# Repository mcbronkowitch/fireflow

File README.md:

# FireFlow — a modulation-first ambient groovebox

A digital instrument built around a single idea: **modulation is the
instrument**. Two symmetric parts, each driven by a performable modulation
engine, feeding a selectable sound source.

It runs today on the desktop and inside VCV Rack. The hardware target is a
**standalone Daisy Patch Submodule prototype**, brought up in milestone M6.

**Build log, audio demos and photos:** [fireflow.ton-k.de](https://fireflow.ton-k.de/)

> **⚠️ Not yet running on hardware.** The modulation engine currently exists
> only as a portable C++ core, verified with the desktop **offline renderer**
> (unit tests + audio/CV render) and playable through the VCV Rack host.
> Selected CPU workloads have been measured on a real Daisy Seed, and the control
> hardware is being measured on a test coupon; the firmware that turns the engine
> into a playable device is milestone M6, and it has not been built.

## What makes it different

The **modulation system is the primary interface**, and the sound engine is
whatever you point it at — not a sound engine you happen to be able to
modulate.

Each part currently points at one of five: a **polyphonic synth voice**, a
**granular texture deck** that granulates live input or a loaded sample,
**WAVE**, a digital-glassy PPG-style wavetable voice, **BODY**, a resonator
that morphs along a physical axis from plucked string through prepared piano to
struck bell, or **BBD**, a voiceless bucket-brigade delay that processes
whatever reaches it — audio input or the other deck — instead of playing
notes. The deck is deliberately not a second melodic instrument — it
is the room the synth part plays in; WAVE covers the bell, vocal-formant,
hollow-resonant, and bright-digital corner; BODY is the struck and bowed one,
and it can be excited by its own echo, by the other deck, or by the audio
input; BBD is the one deck with nothing to trigger — it has no notes, so its
five modulation lanes drive the delay's clock, feedback and mix instead of
pitch and timbre, and its own voice row retunes ATTACK/DECAY/RESONANCE/SUB/
FILT into the delay's freeze, tail, feedback tilt, input level and loss-pole
brightness. All five sit behind the same five modulation lanes and the same
voice row, so no knob goes dead when you flip the engine.

That voice-row **SOURCE** control is contextual — **TIMB** on Synth, **FRAME**
on WAVE, **MATL** on BODY, **ORG** on Sampler, and **DRIVE** on BBD — while
**Detune A/B** remains an independent per-part setting.

On the texture deck, **STEP** walks a `SliceMap` of transients marked while the
buffer is recorded or loaded: each phrase fire spawns one grain on a real
attack in the material. MOTION moves that walk from ordered playback at zero
toward free traversal. **DENS** controls runtime grain overlap; **COLOR**
becomes **FEEL** in STEP, deriving accents from the material, and spreads the
cloud's pitch in FLOW. Material without enough transients falls back to the
even tempo grid automatically, so drones and pads stay playable. FLOW still
moves continuously across the same lanes regardless of engine.

Melodic **STEP** lanes keep two persistent full-pattern snapshots, A and B.
**FORM** chooses how those phrases are composed — TWO MOTIFS, ONE + VAR,
HIERARCHICAL, CALL / RESPONSE, or OSTINATO — while **SONG** independently
arranges them as AAAB, ABAB, ABBB, BUILD, ROTATE, MIRROR, or OFF. Structural
changes land on phrase boundaries; OFF keeps A evolving while B remains stored.
On the Rack panel the PLAY row is **STEP · FORM · SONG · NEW**. NEW rebuilds
the A/B pair and, on a Sampler, also spawns a grain immediately.

Those STEP notes are not all the same note. Each deck already ranks the slots
of its groove, and **DENSE** decides how far down that ranking it fires — so
the first slot to sound is the anchor and the ones DENSE reveals sit under it.
That ranking *is* the accent: it scales how hard a note is struck and how long
it rings (the ring-time half only once **DEC** is up), which gives a dense
pattern a contour instead of a machine pulse. No knob was added for it.

Each of the two **parts** is a **SuperModulator** — one performable macro
surface (RATE, SHAPE, DENSITY, SMOOTH, RANGE, MOD) sitting on top of
**five independent modulation lanes**, one per target. Every lane has its own
phase, its own random stream and its own probability dice, running at a fixed
musical ratio of the master rate. Shared character, independent motion: the
melody can rise while the filter falls. (A single output driving all targets
would just move everything in unison — a tremolo, not an instrument.)

Each lane can run as a smooth LFO (**FLOW**), a stepped sequence (**STEP**), or
grow, loop, or erode over time (**ENTROPY**). A center section -- **MORPH / COUPLE / DRIFT / SPOT / SETTLE** -- makes the
interaction between the two parts playable. One shared **Oliverb**-based
ambient reverb turns the room into an instrument (Doppler SIZE and a DECAY that
blooms past 100 %), while each deck has its own **SEND** dry/send mix into that
shared room (the centre **ROOM** group holds the reverb itself). CV + gate
outputs extend the modulation to the rest of the rack.

The full design intent lives in
[`docs/superpowers/specs/`](docs/superpowers/specs/); this README is a
self-contained summary of it.

## Architecture at a glance

One portable engine core, three hosts. No hardware type ever crosses into
`engine/`, so the exact same code runs in the desktop renderer, the VCV Rack
module, and (later) on the hardware prototype.

`Instrument` (`engine/instrument.h`) is the complete public API: `init(sample_rate)`,
normalized `0..1` parameter setters, and `process(in, out, size)`.

## Try it on the desktop (no hardware)

The engine is fully testable offline. You need a host C++ toolchain
(**clang** or gcc), **CMake**, and **Ninja**. doctest and nlohmann/json are
vendored under `third_party/`, so no test dependencies are fetched.

```bash
# optional: source a local env.sh to put your toolchain on PATH and set CC/CXX
source env.sh

cmake -S . -B build -DCMAKE_BUILD_TYPE=Release
cmake --build build
```

Run the unit tests:

```bash
ctest --test-dir build --output-on-failure
```

Configure with `-DCMAKE_BUILD_TYPE=Release`. Two of the six tests (`spky_tests`
and `ctrl_identity`) compare rendered audio against stored SHA-256 references,
and those were generated from an optimised build — a Debug configuration renders
slightly different floats and fails them with `SYNTH reference moved`.

Render a scenario to audio + a modulation trace. A scenario is a JSON timeline
of parameter changes (see `host/render/scenarios/`):

```bash
./build/render.exe host/render/scenarios/demo_step_melody.json out.wav mods.csv
```

This writes:

- **`out.wav`** — the rendered audio.
- **`mods.csv`** — every lane's output plus pitch CV / gate per part, decimated
  for plotting. Ideal for *seeing* what FLOW / STEP / MELODY actually do.

`demo_step_melody` is a good starting point: a fixed 16-step melody that loops
identically, then varies (GROW) or regenerates into new motivic phrases (RENEW)
as MELODY is dialled off center — and cycles the phrase principle.

## Play it now — VCV Rack (beta)

For a hands-on feel of the concept there's a **VCV Rack plugin** (`host/vcv/`)
that runs the same engine live — turn the knobs and hear the modulation engine
long before the M6 firmware. It's now a **beta**: real, playable Rack modules and
a permanent part of the workflow, not yet a finished instrument.

The plugin ships **two modules over the one engine core**. **FireFlow** is the
full surface: every engine setter on its own knob. **FireFlow HW Draft** is a
design study of the 60 HP hardware panel M6 is heading for, on the same engine.
Details in [`host/vcv/README.md`](host/vcv/README.md).

You can also just listen first: the [build log](https://fireflow.ton-k.de/)
carries recordings from most milestones, next to the story of how they came
about.

**[Download the latest release](https://github.com/mcbronkowitch/fireflow/releases/latest)**
— `.vcvplugin` builds for Windows, Apple Silicon and Linux, currently **2.22.0**
(both modules: Synth, Sampler, WAVE, BODY, BBD and FEED, the independent
FORM/SONG phrase arranger, the STEP mod grid lock, the PACE modulation
time-stretch, the redrawn 60 HP hardware plate with its excursion lamps, the
STEP accent, PULL's chord gravity, and the MOD layer — hold MOD and every
wreathed knob edits its own modulation depth). Unpack into Rack's user plugin
directory and restart Rack.

Building it yourself needs its own toolchain (a native MinGW/GCC compiler, not
the desktop clang path); the build, install and I/O details live in
[`host/vcv/README.md`](host/vcv/README.md).

## Roadmap

| Milestone | Scope | Status |
|-----------|-------|--------|
| **M1** | Portable engine foundation: SuperModulator, five lanes, `Instrument` API, desktop render host + tests | ✅ done |
| **M1.6** | FX: per-part FLUX (tape echo) + GRIT (drive/reduce), shared ambient reverb, FX params as modulation targets | **done** (engine + host) |
| **M2** | Polyphonic synth voice (replaces the M1 test tone) | **done** (engine + host) |
| **M3** | Capture sequencer (freeze the PITCH lane into a loop) | built, then **removed** 2026-07-14 as orthogonal to the melody rework; nothing replaced it |
| **M4** | Center section — MORPH / COUPLE / DRIFT / SPOT / SETTLE | **done** (engine + host) |
| **M4.5** | Ambient reverb v2 — Oliverb port: Doppler SIZE, DECAY > 100 % bloom, TONE; shimmer & LGPL removed | **done** (engine + host) |
| **M4.6** | Dynamics — one-knob comp per part + master limiter w/ master drive (captioned **PUSH** on the panel) | **done** (engine + host) |
| **M4.8** | Reverb dry/wet — equal-power MIX at the master join + clear-on-sleep CPU bypass | **done** (engine + host) |
| **M4.9** | Reverb DIFFUSION knob (replaces DEPTH) — room density 0–0.9, weak line-mod coupling | **done** (engine + host) |
| **M4.10** | Chord layer — COLOR knob, diatonic stacks, voice-leading, live FLOW surface | **done** (engine + hosts; hardware placement deferred) |
| **M5** | Sampler -- the texture deck: granular cloud, live recording + overdub, WAV load/save, Morphagene-style DENS/SCAN/NEW/LEN/ORG controls, clocked slice-groove, FEEL accents, and FLOW cloud dispersion | **done** (engine + hosts; released through 2.11.0) |
| **M5h** | Per-deck **SEND** mix: independent dry/send mix per deck into one shared Oliverb reverb | **done** (engine + VCV panel; released in 2.11.0) |
| **CPU** | Three measured rounds on real hardware: `instrument_worst`'s worst block went from ~156 % of the audio-block budget to 94 %, and back up to 102 % when M5j's tape tap landed (measured at 5.4 % of the block). Since then an optimization ladder (DTCM placement, an ITCM audio hotset, `-O3`) brought the selected gate `instrument_worst_bbd_dtcm` to **96.43 %** of the block on a Daisy Seed, and the whole signal path has been re-measured against it. **The engine's own worst case still does not fit**: on a Patch Submodule `instrument_worst` reads 102.27 % average / 108.62 % maximum, and whether that is a reachable operating point is an open question. Two more caveats live in `docs/roadmap.md`: every workload is more expensive on the submodule than on the Seed (reserve 2.17 points, so no Seed figure may be quoted for a submodule claim), and the intended ITCM placement does not currently link at the optimization level that ships. A debug probe is no longer needed — the bench also reports over USB-CDC. Method and every number in [`bench/`](bench/README.md) and [`docs/bench/`](docs/bench/) | **done** (ongoing as a tool) |
| **M5i** | WAVE: four-voice PPG-style wavetable part engine | **done** (engine + renderer + VCV; 65,024-byte mapped-QSPI bank; hardware-gated; released in 2.13.0) |
| **+ FORM/SONG** | Persistent A/B phrase snapshots: five FORM phrase engines plus AAAB, ABAB, ABBB, BUILD, ROTATE, MIRROR, and OFF SONG arrangements; boundary-safe changes and legacy patch migration | **done** (engine + renderer + VCV; released in 2.13.1) |
| **M5j** | BODY: one-voice-per-deck resonator part engine, morphing string -> metal -> bell, with a sympathetic excitation bus | **done** (engine + renderer + VCV; hardware-gated: `body_2x4` 295078 cycles, 30.7 % of the block, inside the spec's 29-32 % prediction and cheaper than SYNTH) |
| **BBD** | A bucket-brigade delay model, where the clock rate *is* the delay time — so RATE bends stored pitch **only transiently, while it moves**: held steady, a bucket-brigade line's pitch is unity at any clock rate. It first replaced FLUX's tape echo everywhere and now lives on as the fifth part engine only; FLUX itself is a plain tape echo again. `FXT_FLUX_TIME` is a genuine chorus/vibrato modulation lane, and STAGES has moved onto the BBD deck's own pitch lane, captioned **BEND** on the panel | **done** (engine + renderer + VCV; released in 2.17.0/2.17.1, measured on hardware — `inst_bbd_engine_worst` 96.91 % of the block at `-O3`) |
| **Modulation reachability** | Four rounds that made the modulation surface mean what it says: **PACE**, one global time-stretch from ×1/32 to ×4, because TEMPO was inert in the free world and TIDE never reached the melodic lane; the **FLOW melody engine**, so the free mode's melodic lane walks an 8-slot phrase instead of a continuous LFO; the same phrase in **STEP**, which makes FORM and SONG audible at every SHAPE position instead of only above 0.75; and **SMOOTH as a fraction of the lane interval** rather than absolute seconds, so the knob means the same thing at every rate | **done** (engine + hosts; released in 2.21.2) |
| **60 HP plate** | The hardware panel, drawn and playable in Rack as the second module: seven engine-grounded groups, eight CV inputs under the knobs they drive, and a dark anodised plate with framed fields and numbered legends | **done** as a design study (released in 2.21.2/2.21.3; still labelled `DRAFT`, no hardware ordered) |
| **STEP accent** | STEP notes get a contour from the groove rank the deck already computes: the anchor slot is loudest and longest, the slots DENSE reveals sit under it, on velocity and — once DEC is up — on ring time. No new control, no new randomness, FLOW unaffected; SYNTH, WAVE and BODY only | **done** (engine; released in 2.21.4) |
| **LED feedback** | What the panel shows while it runs: a lamp tracks the modulation **excursion**, never the knob position — one per texture lane, plus a phrase lamp per deck, a ceiling lamp for the limiter's audible onset, and the two modifier lamps. Nineteen lamps on the hardware plate, up from ten | **done** (engine + VCV `FireflowHW`; released in 2.21.5; four brightness constants still wait on real hardware) |
| **FEED** | Sixth part engine: a ring of six two-operator FM pairs per deck, free-running, where BOND morphs each modulator's input from its own feedback into its neighbour's output — the motion is the coupling, not an LFO on top | **done** (engine + hosts; released in 2.21.6; measured on a Patch Submodule, seventeen by-ear constants still first-try) |
| **M5l** | PULL: chord gravity between the two decks — a bipolar centre knob draws one deck's melody onto the other's sounding chord | **done** (engine + both VCV panels; released in 2.21.8; no listening pass yet) |
| **MOD layer** | Hold MOD and every wreathed knob shows and edits its own modulation depth instead of its sound value. The depth knobs are bipolar: right of noon the lane's continuous output, left of noon the same lane sampled and held on its own slots, noon off | **done** (engine + VCV `FireflowHW`; released in 2.21.7 and 2.21.10) |
| **AIR** | Noise/formant texture engine (working title): filtered noise through a resonant bank — wind, breath, vowel colours without sample material | planned (no spec yet) |
| **M5k** | ZAP: monophonic percussion part engine | planned (spec ready; not implemented) |
| **M6** | Hardware prototype: bring-up on a Daisy Patch Submodule — panel, controls, LEDs, CV/gate I/O, preset persistence | planned after AIR and M5k (panel design **done**, see above; **bring-up under way on a test coupon** — built 2026-09-17, measured in five rounds up to 2026-09-28; the panel scan's part 1 is built and measured on the coupon, part 2, the panel's table, waits on the pin map of Rev A, one board since 2026-09-28) |

Per-milestone detail and current status live in [`docs/roadmap.md`](docs/roadmap.md).

## Hardware prototype (M6)

The instrument's own hardware is a **standalone Daisy Patch Submodule**
prototype — panel, controls, LEDs, CV/gate I/O and preset persistence — planned
as milestone **M6**, after the two remaining engine milestones. Its **panel is
designed**, and you can turn it: the plugin's second module, **FireFlow HW
Draft**, is that 60 HP surface on the same engine, generated from
`host/vcv/res/gen_hw_panel.py` and guarded against the spec's own coordinates.

The **bring-up is under way on a test coupon** (`hardware/coupon/`): a small
board carrying the real multiplexers, shift registers, pots and reference
dividers, built on 2026-09-17 and driven by the probe firmware in `shell/`.
Five measurement rounds have run on it — settle time, crosstalk, the codec's
tone, the wait between conversions, and the pots themselves — each written up
under `docs/hardware/` (`settle-measured.md` … `pots-measured.md`). **Part 1 of
the panel scan is built and measured on the coupon**: it reads the mux pattern
cleanly and plays the engine from three of the coupon's pots
(`docs/hardware/scan-measured.md`). **Part 2**, the table for a whole panel —
70 pots, keycaps, LEDs — waits on the pin map of Rev A, which is one board
since 2026-09-28.

CPU headroom on the target MCU is not guesswork, though. Selected workloads are
measured on real Daisy hardware (a Daisy Seed, which carries the same STM32H750
at 480 MHz as the Patch Submodule) — method and every number in
[`bench/`](bench/README.md) and [`docs/bench/`](docs/bench/).

The original Spotykach firmware this project started from was removed from the
tree on 2026-09-29; [`docs/upstream-firmware.md`](docs/upstream-firmware.md)
says where it went and what of it stayed.

## License & credits

MIT — see [`LICENSE`](LICENSE) (Copyright © 2026 Synthux Academy, Bastian Tonk).

FireFlow began as a fork of
[Synthux-Academy/Spotykach](https://github.com/Synthux-Academy/Spotykach), the
official firmware for the Spotykach hardware, and reuses parts of it; it is now
an independent project with its own hardware target. It was called **spotymod**
until 2026-08-04 — releases up to and including 2.18.x carry that name.
Bundled and submodule dependencies are documented in
[`THIRD_PARTY.md`](THIRD_PARTY.md). Original firmware credits are in
[`CREDITS.md`](CREDITS.md).

Built with AI pair-programming — the **HAL 9000** co-author in the git history
is [Claude](https://www.anthropic.com/claude) (Anthropic). 🔴

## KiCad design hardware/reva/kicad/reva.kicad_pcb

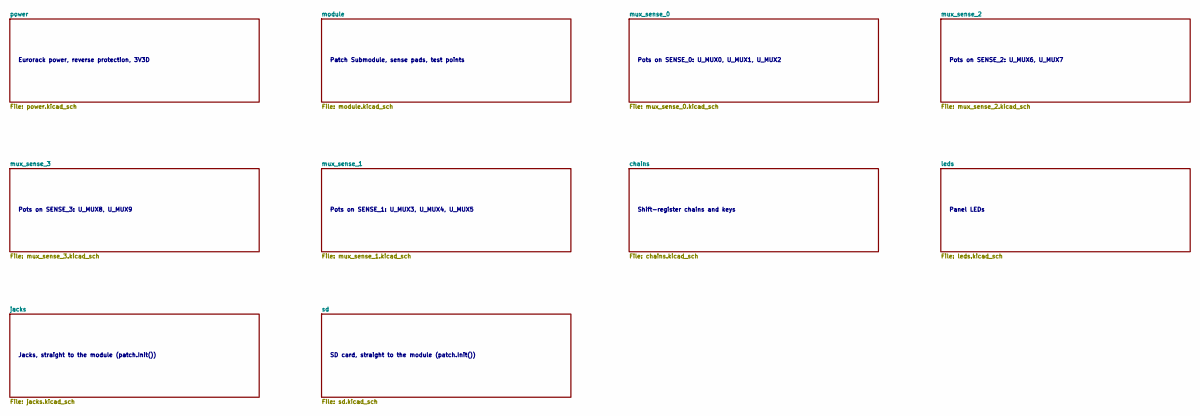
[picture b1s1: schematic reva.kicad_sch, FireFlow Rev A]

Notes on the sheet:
Eurorack power, reverse protection, 3V3D
Patch Submodule, sense pads, test points
Pots on SENSE_0: U_MUX0, U_MUX1, U_MUX2
Pots on SENSE_2: U_MUX6, U_MUX7
Pots on SENSE_3: U_MUX8, U_MUX9
Pots on SENSE_1: U_MUX3, U_MUX4, U_MUX5
Shift-register chains and keys
Panel LEDs
Jacks, straight to the module (patch.Init())
SD card, straight to the module (patch.Init())

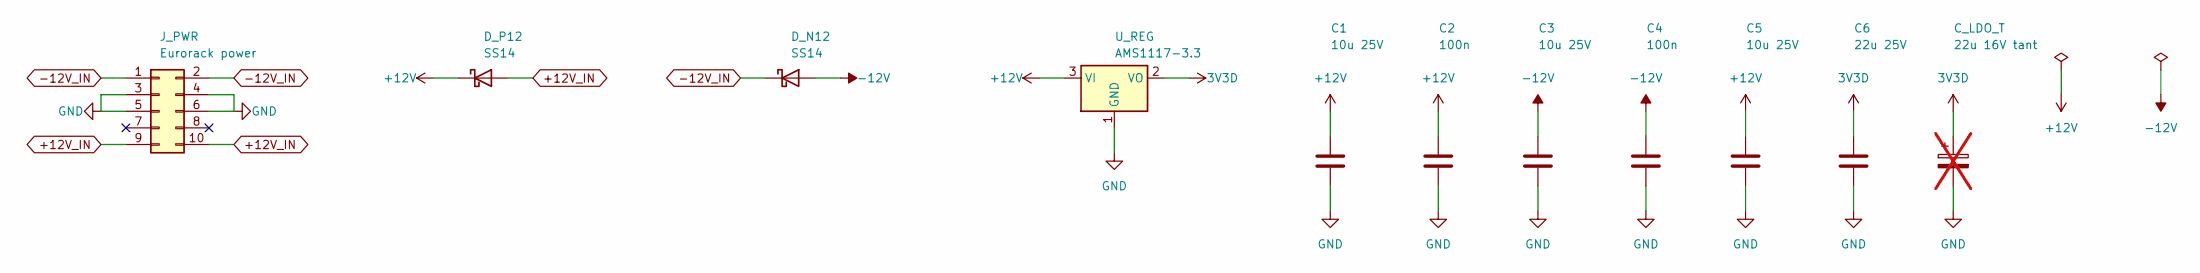
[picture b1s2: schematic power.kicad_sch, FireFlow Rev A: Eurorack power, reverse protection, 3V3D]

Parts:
C1, C3, C5: 10u 25V; C_0805_2012Metric; LCSC C15850
C2, C4: 100n; C_0603_1608Metric; LCSC C14663
C6: 22u 25V; C_0805_2012Metric; LCSC C45783
C_LDO_T: 22u 16V tant; CP_EIA-6032-28_Kemet-C; LCSC C1967941; not fitted
D_N12: SS14; D_SMA; LCSC C2480
D_P12: SS14; D_SMA; LCSC C2480
J_PWR: Eurorack power; IDC-Header_2x05_P2.54mm_Vertical
U_REG: AMS1117-3.3; SOT-223-3_TabPin2; LCSC C6186

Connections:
3V3D: C6.1, C_LDO_T.1, U_REG.2 (VO); also elsewhere on the board
+12V: C1.1, C2.1, C5.1, D_P12.1 (K), U_REG.3 (VI); also elsewhere on the board
+12V_IN: D_P12.2 (A), J_PWR.9, J_PWR.10
-12V: C3.1, C4.1, D_N12.2 (A); also elsewhere on the board
-12V_IN: D_N12.1 (K), J_PWR.1, J_PWR.2
GND: C1.2, C2.2, C3.2, C4.2, C5.2, C6.2, C_LDO_T.2, J_PWR.3, J_PWR.4, J_PWR.5, J_PWR.6, U_REG.1 (GND); also elsewhere on the board

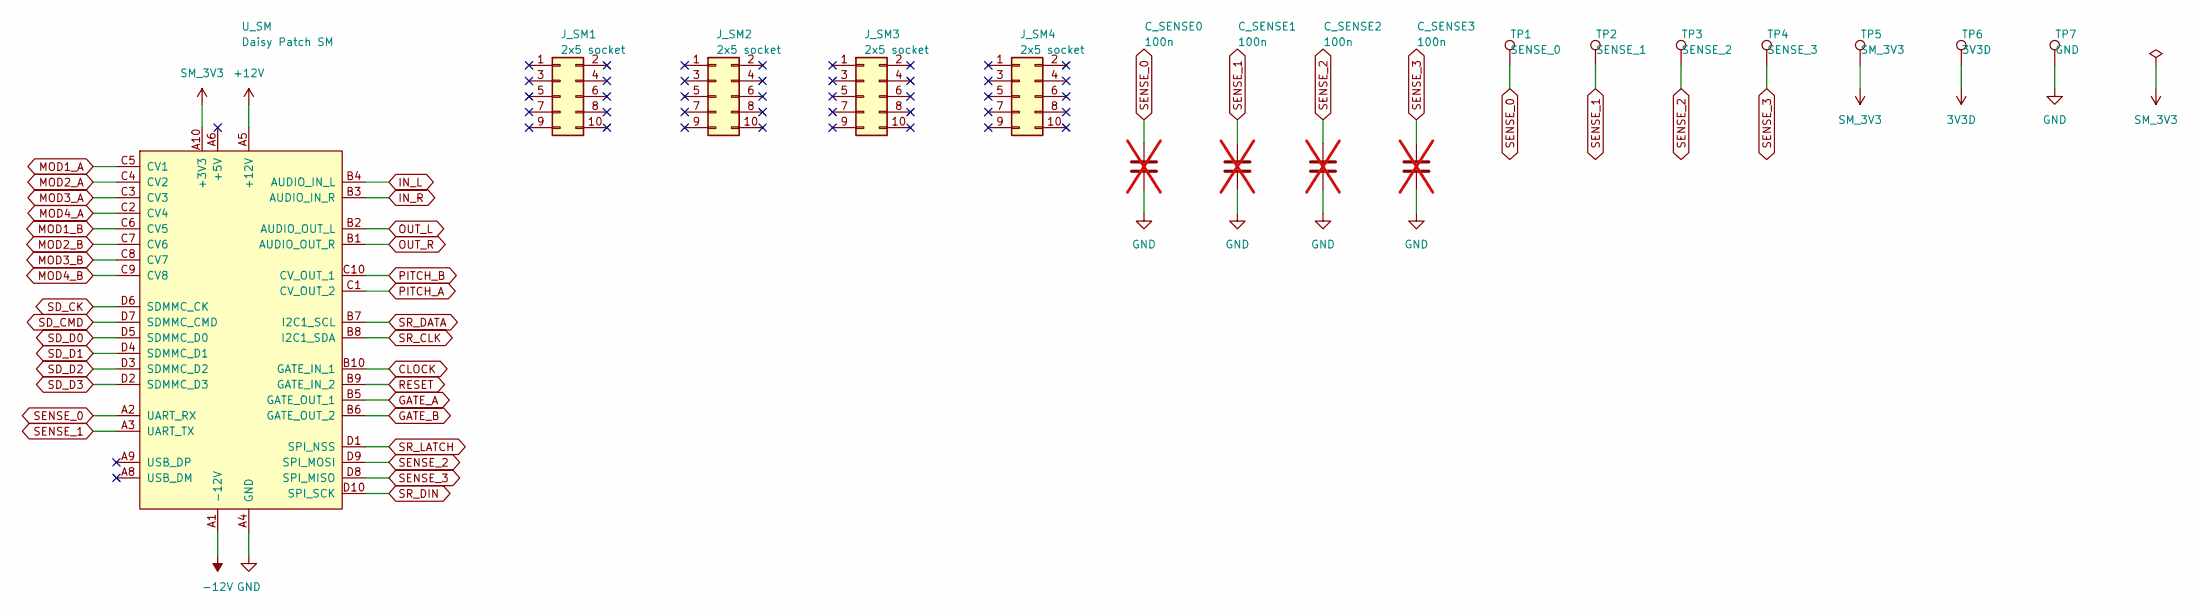
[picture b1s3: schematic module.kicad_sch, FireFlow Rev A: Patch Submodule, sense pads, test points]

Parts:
C_SENSE0, C_SENSE1, C_SENSE2, C_SENSE3: 100n; C_0603_1608Metric; LCSC C14663; not fitted
J_SM1, J_SM2, J_SM3, J_SM4: 2x5 socket
TP1: SENSE_0; TestPoint_Pad_D1.5mm
TP2: SENSE_1; TestPoint_Pad_D1.5mm
TP3: SENSE_2; TestPoint_Pad_D1.5mm
TP4: SENSE_3; TestPoint_Pad_D1.5mm
TP5: SM_3V3; TestPoint_Pad_D1.5mm
TP6: 3V3D; TestPoint_Pad_D1.5mm
TP7: GND; TestPoint_Pad_D1.5mm
U_SM: Daisy Patch SM; DAISY_PATCH_SM

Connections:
3V3D: TP6.1; also elsewhere on the board
+12V: U_SM.A5 (+12V); also elsewhere on the board
-12V: U_SM.A1 (-12V); also elsewhere on the board
CLOCK: U_SM.B10 (GATE_IN_1); also elsewhere on the board
GATE_A: U_SM.B5 (GATE_OUT_1); also elsewhere on the board
GATE_B: U_SM.B6 (GATE_OUT_2); also elsewhere on the board
GND: C_SENSE0.2, C_SENSE1.2, C_SENSE2.2, C_SENSE3.2, TP7.1, U_SM.A4 (GND), U_SM.A7 (GND); also elsewhere on the board
IN_L: U_SM.B4 (AUDIO_IN_L); also elsewhere on the board
IN_R: U_SM.B3 (AUDIO_IN_R); also elsewhere on the board
MOD1_A: U_SM.C5 (CV1); also elsewhere on the board
MOD1_B: U_SM.C6 (CV5); also elsewhere on the board
MOD2_A: U_SM.C4 (CV2); also elsewhere on the board
MOD2_B: U_SM.C7 (CV6); also elsewhere on the board
MOD3_A: U_SM.C3 (CV3); also elsewhere on the board
MOD3_B: U_SM.C8 (CV7); also elsewhere on the board
MOD4_A: U_SM.C2 (CV4); also elsewhere on the board
MOD4_B: U_SM.C9 (CV8); also elsewhere on the board
OUT_L: U_SM.B2 (AUDIO_OUT_L); also elsewhere on the board
OUT_R: U_SM.B1 (AUDIO_OUT_R); also elsewhere on the board
PITCH_A: U_SM.C1 (CV_OUT_2); also elsewhere on the board
PITCH_B: U_SM.C10 (CV_OUT_1); also elsewhere on the board
RESET: U_SM.B9 (GATE_IN_2); also elsewhere on the board
SD_CK: U_SM.D6 (SDMMC_CK); also elsewhere on the board
SD_CMD: U_SM.D7 (SDMMC_CMD); also elsewhere on the board
SD_D0: U_SM.D5 (SDMMC_D0); also elsewhere on the board
SD_D1: U_SM.D4 (SDMMC_D1); also elsewhere on the board
SD_D2: U_SM.D3 (SDMMC_D2); also elsewhere on the board
SD_D3: U_SM.D2 (SDMMC_D3); also elsewhere on the board
SENSE_0: C_SENSE0.1, TP1.1, U_SM.A2 (UART_RX); also elsewhere on the board
SENSE_1: C_SENSE1.1, TP2.1, U_SM.A3 (UART_TX); also elsewhere on the board
SENSE_2: C_SENSE2.1, TP3.1, U_SM.D9 (SPI_MOSI); also elsewhere on the board
SENSE_3: C_SENSE3.1, TP4.1, U_SM.D8 (SPI_MISO); also elsewhere on the board
SM_3V3: TP5.1, U_SM.A10 (+3V3); also elsewhere on the board
SR_CLK: U_SM.B8 (I2C1_SDA); also elsewhere on the board
SR_DATA: U_SM.B7 (I2C1_SCL); also elsewhere on the board
SR_DIN: U_SM.D10 (SPI_SCK); also elsewhere on the board
SR_LATCH: U_SM.D1 (SPI_NSS); also elsewhere on the board

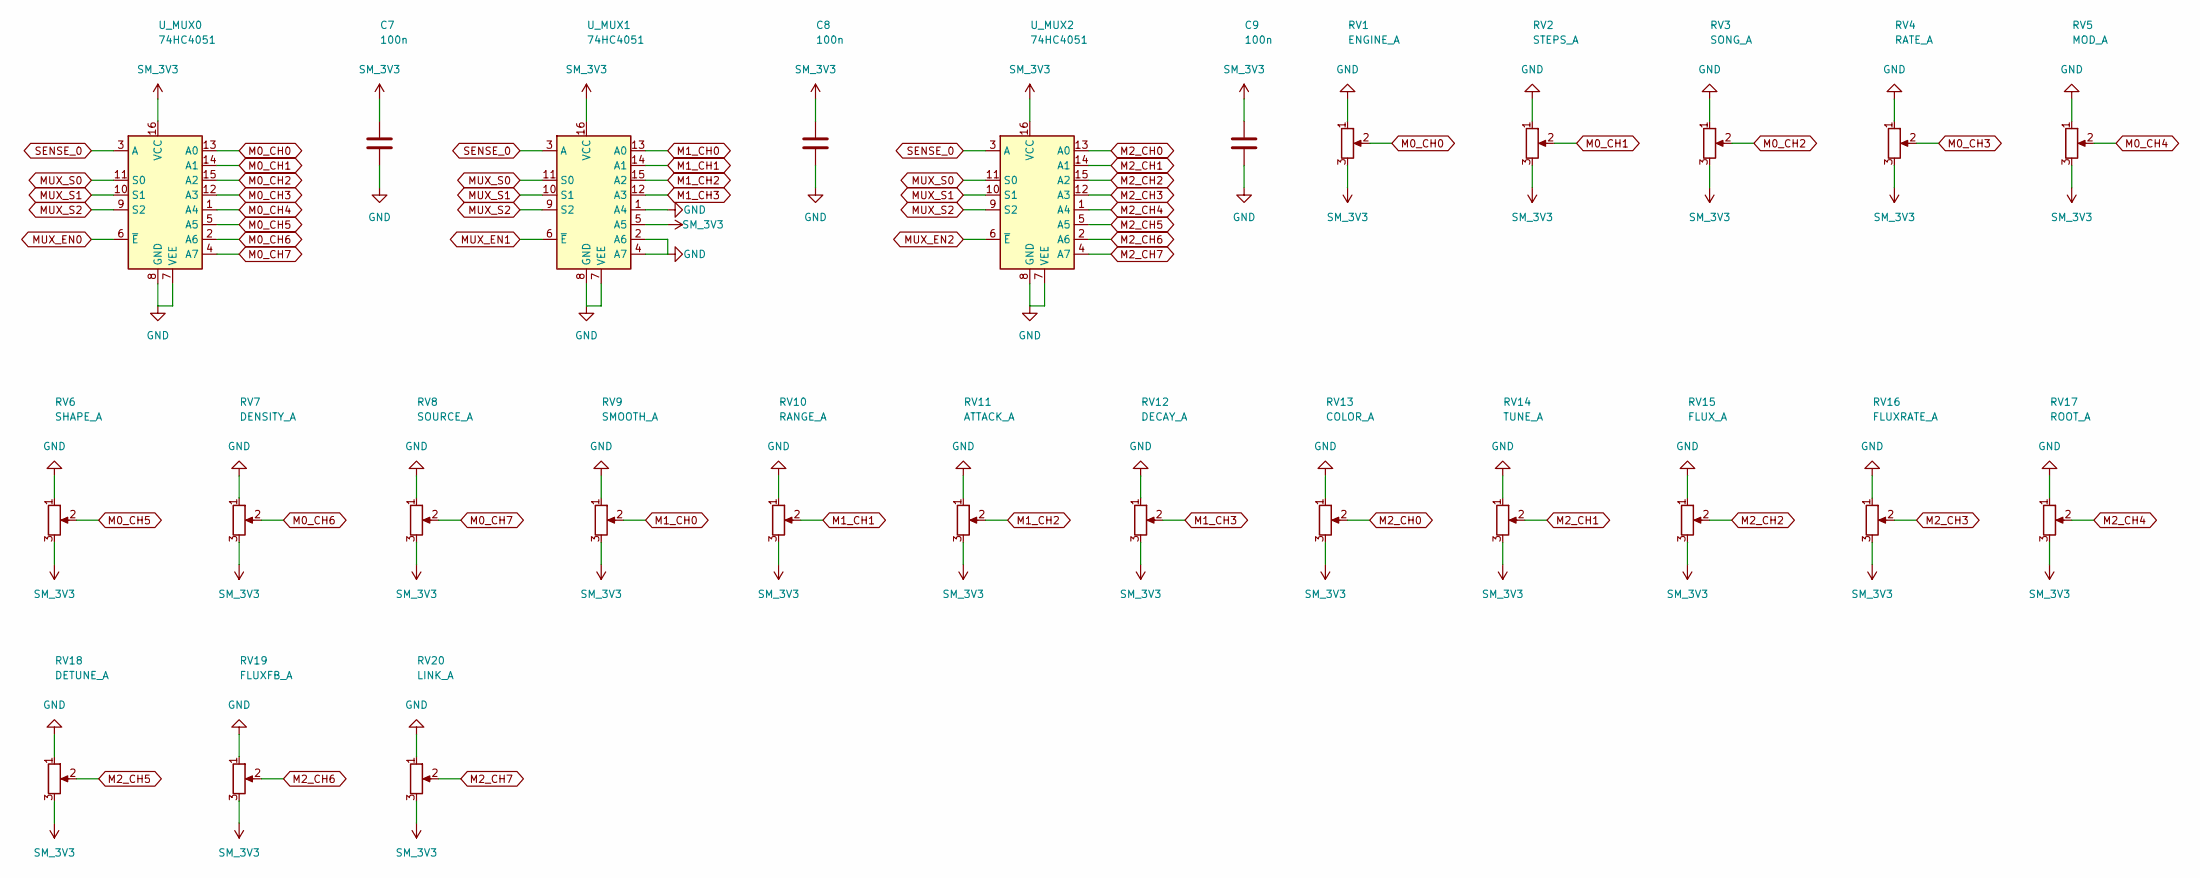
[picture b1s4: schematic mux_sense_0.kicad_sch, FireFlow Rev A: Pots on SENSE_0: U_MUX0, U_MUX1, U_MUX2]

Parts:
C7, C8, C9: 100n; C_0603_1608Metric; LCSC C14663
RV1: ENGINE_A; Potentiometer_Alpha_RD901F-40-00D_Single_Vertical
RV2: STEPS_A; Potentiometer_Alpha_RD901F-40-00D_Single_Vertical
RV3: SONG_A; Potentiometer_Alpha_RD901F-40-00D_Single_Vertical
RV4: RATE_A; Potentiometer_Alpha_RD901F-40-00D_Single_Vertical
RV5: MOD_A; Potentiometer_Alpha_RD901F-40-00D_Single_Vertical
RV6: SHAPE_A; Potentiometer_Alpha_RD901F-40-00D_Single_Vertical
RV7: DENSITY_A; Potentiometer_Alpha_RD901F-40-00D_Single_Vertical
RV8: SOURCE_A; Potentiometer_Alpha_RD901F-40-00D_Single_Vertical
RV9: SMOOTH_A; Potentiometer_Alpha_RD901F-40-00D_Single_Vertical
RV10: RANGE_A; Potentiometer_Alpha_RD901F-40-00D_Single_Vertical
RV11: ATTACK_A; Potentiometer_Alpha_RD901F-40-00D_Single_Vertical
RV12: DECAY_A; Potentiometer_Alpha_RD901F-40-00D_Single_Vertical
RV13: COLOR_A; Potentiometer_Alpha_RD901F-40-00D_Single_Vertical
RV14: TUNE_A; Potentiometer_Alpha_RD901F-40-00D_Single_Vertical
RV15: FLUX_A; Potentiometer_Alpha_RD901F-40-00D_Single_Vertical
RV16: FLUXRATE_A; Potentiometer_Alpha_RD901F-40-00D_Single_Vertical
RV17: ROOT_A; Potentiometer_Alpha_RD901F-40-00D_Single_Vertical
RV18: DETUNE_A; Potentiometer_Alpha_RD901F-40-00D_Single_Vertical
RV19: FLUXFB_A; Potentiometer_Alpha_RD901F-40-00D_Single_Vertical
RV20: LINK_A; Potentiometer_Alpha_RD901F-40-00D_Single_Vertical
U_MUX0, U_MUX1, U_MUX2: 74HC4051; SOIC-16_3.9x9.9mm_P1.27mm; LCSC C9386

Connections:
GND: C7.2, C8.2, C9.2, RV1.1, RV2.1, RV3.1, RV4.1, RV5.1, RV6.1, RV7.1, RV8.1, RV9.1, RV10.1, RV11.1, RV12.1, RV13.1, RV14.1, RV15.1, RV16.1, RV17.1, RV18.1, RV19.1, RV20.1, U_MUX0.7 (VEE), U_MUX0.8 (GND), U_MUX1.1 (A4), U_MUX1.2 (A6), U_MUX1.4 (A7), U_MUX1.7 (VEE), U_MUX1.8 (GND), U_MUX2.7 (VEE), U_MUX2.8 (GND); also elsewhere on the board
M0_CH0: RV1.2, U_MUX0.13 (A0)
M0_CH1: RV2.2, U_MUX0.14 (A1)
M0_CH2: RV3.2, U_MUX0.15 (A2)
M0_CH3: RV4.2, U_MUX0.12 (A3)
M0_CH4: RV5.2, U_MUX0.1 (A4)
M0_CH5: RV6.2, U_MUX0.5 (A5)
M0_CH6: RV7.2, U_MUX0.2 (A6)
M0_CH7: RV8.2, U_MUX0.4 (A7)
M1_CH0: RV9.2, U_MUX1.13 (A0)
M1_CH1: RV10.2, U_MUX1.14 (A1)
M1_CH2: RV11.2, U_MUX1.15 (A2)
M1_CH3: RV12.2, U_MUX1.12 (A3)
M2_CH0: RV13.2, U_MUX2.13 (A0)
M2_CH1: RV14.2, U_MUX2.14 (A1)
M2_CH2: RV15.2, U_MUX2.15 (A2)
M2_CH3: RV16.2, U_MUX2.12 (A3)
M2_CH4: RV17.2, U_MUX2.1 (A4)
M2_CH5: RV18.2, U_MUX2.5 (A5)
M2_CH6: RV19.2, U_MUX2.2 (A6)
M2_CH7: RV20.2, U_MUX2.4 (A7)
MUX_EN0: U_MUX0.6 (~E); also elsewhere on the board
MUX_EN1: U_MUX1.6 (~E); also elsewhere on the board
MUX_EN2: U_MUX2.6 (~E); also elsewhere on the board
MUX_S0: U_MUX0.11 (S0), U_MUX1.11 (S0), U_MUX2.11 (S0); also elsewhere on the board
MUX_S1: U_MUX0.10 (S1), U_MUX1.10 (S1), U_MUX2.10 (S1); also elsewhere on the board
MUX_S2: U_MUX0.9 (S2), U_MUX1.9 (S2), U_MUX2.9 (S2); also elsewhere on the board
SENSE_0: U_MUX0.3 (A), U_MUX1.3 (A), U_MUX2.3 (A); also elsewhere on the board
SM_3V3: C7.1, C8.1, C9.1, RV1.3, RV2.3, RV3.3, RV4.3, RV5.3, RV6.3, RV7.3, RV8.3, RV9.3, RV10.3, RV11.3, RV12.3, RV13.3, RV14.3, RV15.3, RV16.3, RV17.3, RV18.3, RV19.3, RV20.3, U_MUX0.16 (VCC), U_MUX1.5 (A5), U_MUX1.16 (VCC), U_MUX2.16 (VCC); also elsewhere on the board

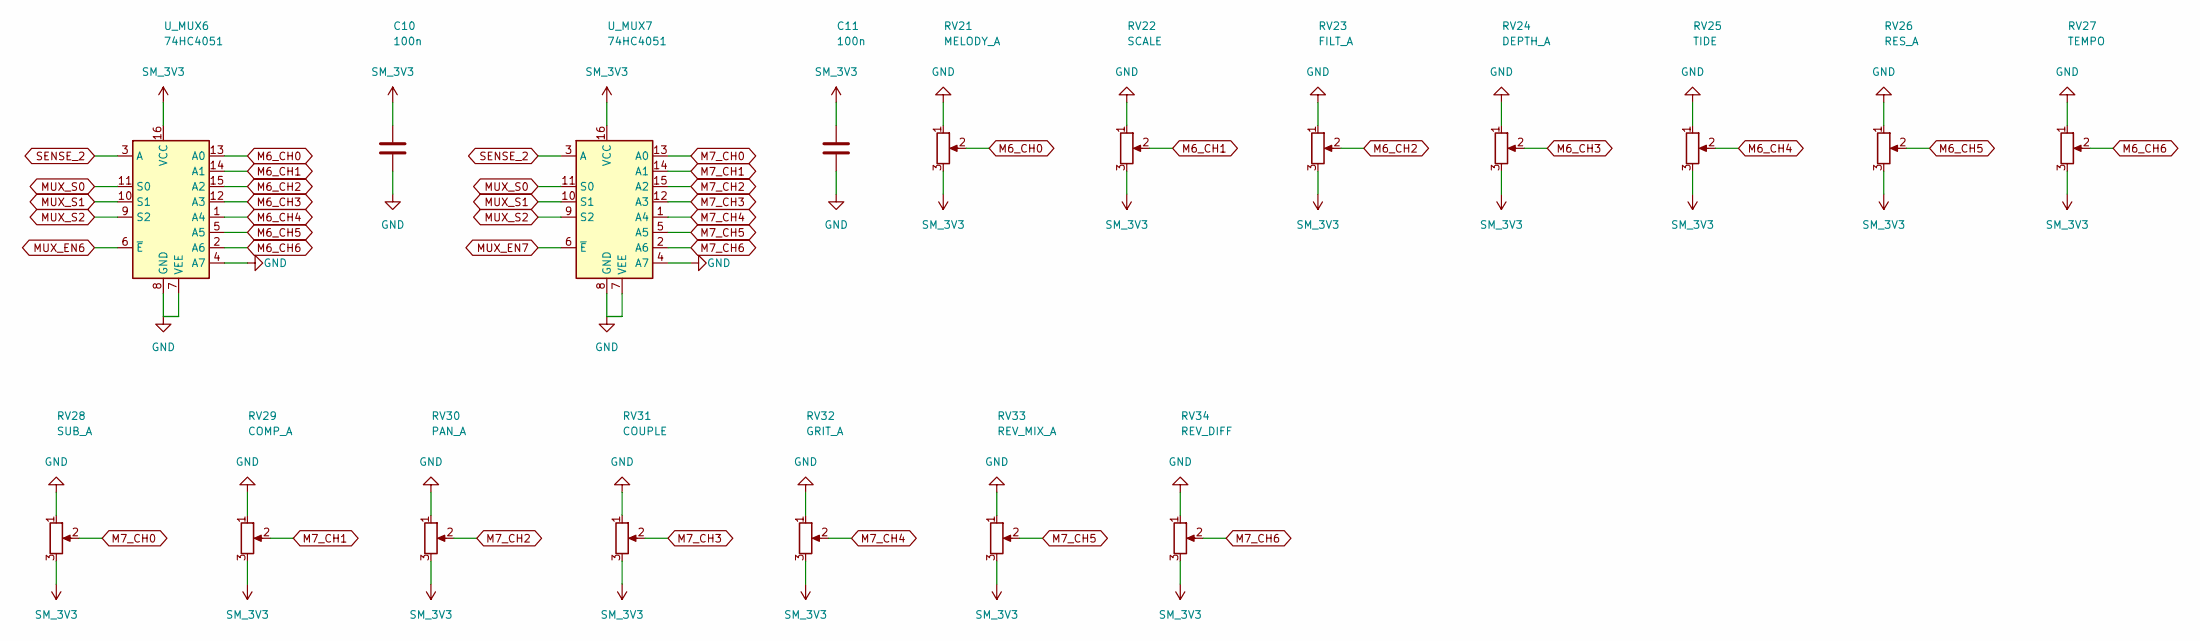
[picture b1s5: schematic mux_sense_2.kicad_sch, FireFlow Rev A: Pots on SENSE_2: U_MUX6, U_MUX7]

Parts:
C10, C11: 100n; C_0603_1608Metric; LCSC C14663
RV21: MELODY_A; Potentiometer_Alpha_RD901F-40-00D_Single_Vertical
RV22: SCALE; Potentiometer_Alpha_RD901F-40-00D_Single_Vertical
RV23: FILT_A; Potentiometer_Alpha_RD901F-40-00D_Single_Vertical
RV24: DEPTH_A; Potentiometer_Alpha_RD901F-40-00D_Single_Vertical
RV25: TIDE; Potentiometer_Alpha_RD901F-40-00D_Single_Vertical
RV26: RES_A; Potentiometer_Alpha_RD901F-40-00D_Single_Vertical
RV27: TEMPO; Potentiometer_Alpha_RD901F-40-00D_Single_Vertical
RV28: SUB_A; Potentiometer_Alpha_RD901F-40-00D_Single_Vertical
RV29: COMP_A; Potentiometer_Alpha_RD901F-40-00D_Single_Vertical
RV30: PAN_A; Potentiometer_Alpha_RD901F-40-00D_Single_Vertical
RV31: COUPLE; Potentiometer_Alpha_RD901F-40-00D_Single_Vertical
RV32: GRIT_A; Potentiometer_Alpha_RD901F-40-00D_Single_Vertical
RV33: REV_MIX_A; Potentiometer_Alpha_RD901F-40-00D_Single_Vertical
RV34: REV_DIFF; Potentiometer_Alpha_RD901F-40-00D_Single_Vertical
U_MUX6, U_MUX7: 74HC4051; SOIC-16_3.9x9.9mm_P1.27mm; LCSC C9386

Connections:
GND: C10.2, C11.2, RV21.1, RV22.1, RV23.1, RV24.1, RV25.1, RV26.1, RV27.1, RV28.1, RV29.1, RV30.1, RV31.1, RV32.1, RV33.1, RV34.1, U_MUX6.4 (A7), U_MUX6.7 (VEE), U_MUX6.8 (GND), U_MUX7.4 (A7), U_MUX7.7 (VEE), U_MUX7.8 (GND); also elsewhere on the board
M6_CH0: RV21.2, U_MUX6.13 (A0)
M6_CH1: RV22.2, U_MUX6.14 (A1)
M6_CH2: RV23.2, U_MUX6.15 (A2)
M6_CH3: RV24.2, U_MUX6.12 (A3)
M6_CH4: RV25.2, U_MUX6.1 (A4)
M6_CH5: RV26.2, U_MUX6.5 (A5)
M6_CH6: RV27.2, U_MUX6.2 (A6)
M7_CH0: RV28.2, U_MUX7.13 (A0)
M7_CH1: RV29.2, U_MUX7.14 (A1)
M7_CH2: RV30.2, U_MUX7.15 (A2)
M7_CH3: RV31.2, U_MUX7.12 (A3)
M7_CH4: RV32.2, U_MUX7.1 (A4)
M7_CH5: RV33.2, U_MUX7.5 (A5)
M7_CH6: RV34.2, U_MUX7.2 (A6)
MUX_EN6: U_MUX6.6 (~E); also elsewhere on the board
MUX_EN7: U_MUX7.6 (~E); also elsewhere on the board
MUX_S0: U_MUX6.11 (S0), U_MUX7.11 (S0); also elsewhere on the board
MUX_S1: U_MUX6.10 (S1), U_MUX7.10 (S1); also elsewhere on the board
MUX_S2: U_MUX6.9 (S2), U_MUX7.9 (S2); also elsewhere on the board
SENSE_2: U_MUX6.3 (A), U_MUX7.3 (A); also elsewhere on the board
SM_3V3: C10.1, C11.1, RV21.3, RV22.3, RV23.3, RV24.3, RV25.3, RV26.3, RV27.3, RV28.3, RV29.3, RV30.3, RV31.3, RV32.3, RV33.3, RV34.3, U_MUX6.16 (VCC), U_MUX7.16 (VCC); also elsewhere on the board

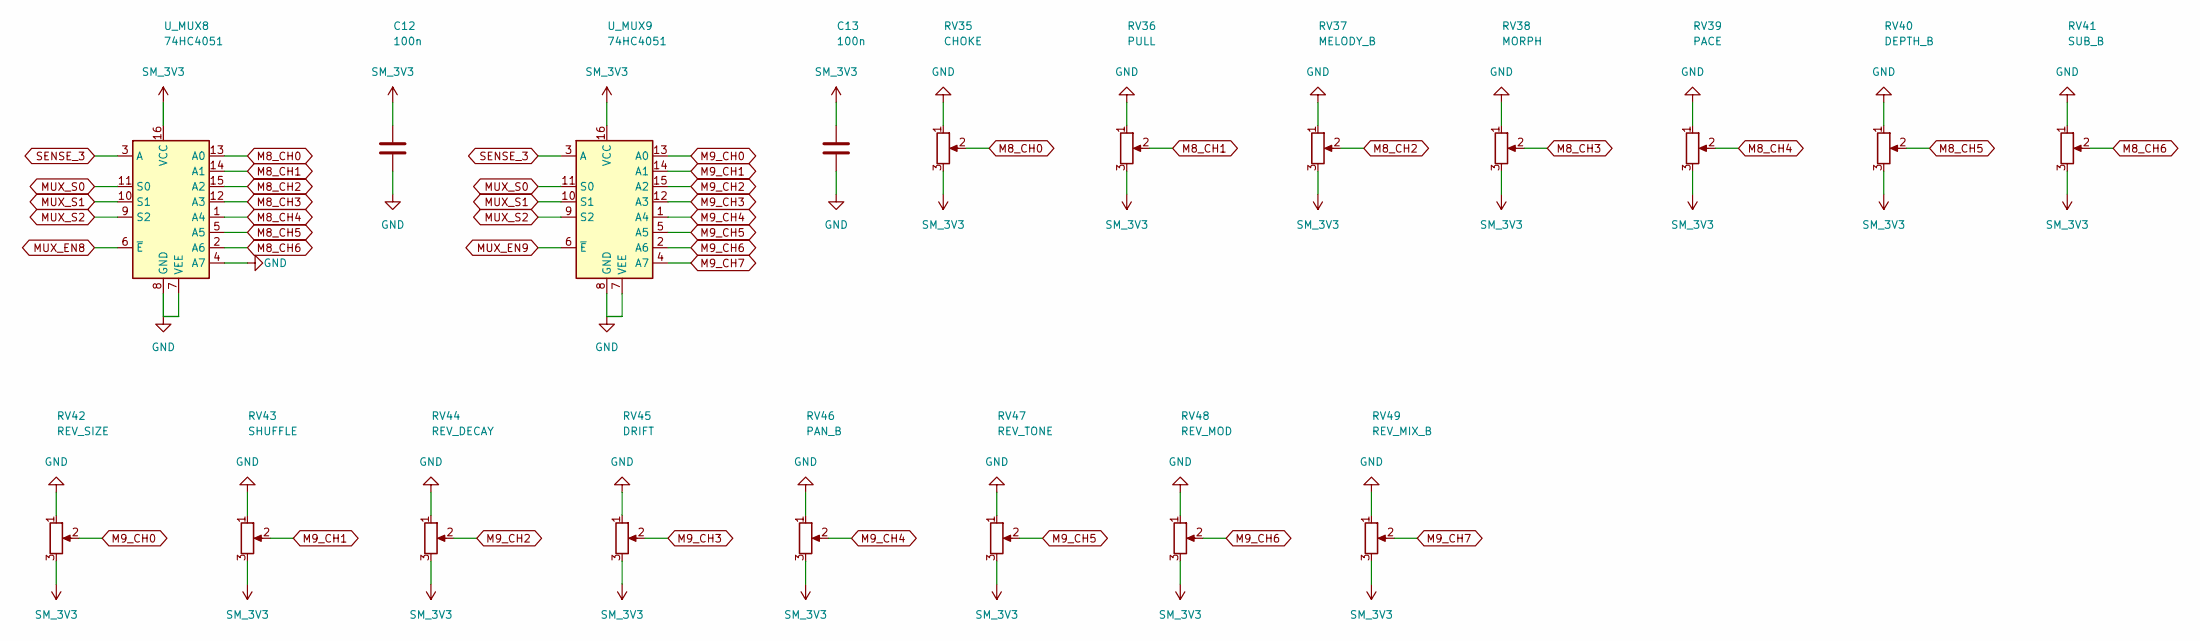
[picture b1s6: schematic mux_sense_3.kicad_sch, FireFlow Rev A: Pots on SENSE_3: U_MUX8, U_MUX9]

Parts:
C12, C13: 100n; C_0603_1608Metric; LCSC C14663
RV35: CHOKE; Potentiometer_Alpha_RD901F-40-00D_Single_Vertical
RV36: PULL; Potentiometer_Alpha_RD901F-40-00D_Single_Vertical
RV37: MELODY_B; Potentiometer_Alpha_RD901F-40-00D_Single_Vertical
RV38: MORPH; Potentiometer_Alpha_RD901F-40-00D_Single_Vertical
RV39: PACE; Potentiometer_Alpha_RD901F-40-00D_Single_Vertical
RV40: DEPTH_B; Potentiometer_Alpha_RD901F-40-00D_Single_Vertical
RV41: SUB_B; Potentiometer_Alpha_RD901F-40-00D_Single_Vertical
RV42: REV_SIZE; Potentiometer_Alpha_RD901F-40-00D_Single_Vertical
RV43: SHUFFLE; Potentiometer_Alpha_RD901F-40-00D_Single_Vertical
RV44: REV_DECAY; Potentiometer_Alpha_RD901F-40-00D_Single_Vertical
RV45: DRIFT; Potentiometer_Alpha_RD901F-40-00D_Single_Vertical
RV46: PAN_B; Potentiometer_Alpha_RD901F-40-00D_Single_Vertical
RV47: REV_TONE; Potentiometer_Alpha_RD901F-40-00D_Single_Vertical
RV48: REV_MOD; Potentiometer_Alpha_RD901F-40-00D_Single_Vertical
RV49: REV_MIX_B; Potentiometer_Alpha_RD901F-40-00D_Single_Vertical
U_MUX8, U_MUX9: 74HC4051; SOIC-16_3.9x9.9mm_P1.27mm; LCSC C9386

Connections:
GND: C12.2, C13.2, RV35.1, RV36.1, RV37.1, RV38.1, RV39.1, RV40.1, RV41.1, RV42.1, RV43.1, RV44.1, RV45.1, RV46.1, RV47.1, RV48.1, RV49.1, U_MUX8.4 (A7), U_MUX8.7 (VEE), U_MUX8.8 (GND), U_MUX9.7 (VEE), U_MUX9.8 (GND); also elsewhere on the board
M8_CH0: RV35.2, U_MUX8.13 (A0)
M8_CH1: RV36.2, U_MUX8.14 (A1)
M8_CH2: RV37.2, U_MUX8.15 (A2)
M8_CH3: RV38.2, U_MUX8.12 (A3)
M8_CH4: RV39.2, U_MUX8.1 (A4)
M8_CH5: RV40.2, U_MUX8.5 (A5)
M8_CH6: RV41.2, U_MUX8.2 (A6)
M9_CH0: RV42.2, U_MUX9.13 (A0)
M9_CH1: RV43.2, U_MUX9.14 (A1)
M9_CH2: RV44.2, U_MUX9.15 (A2)
M9_CH3: RV45.2, U_MUX9.12 (A3)
M9_CH4: RV46.2, U_MUX9.1 (A4)
M9_CH5: RV47.2, U_MUX9.5 (A5)
M9_CH6: RV48.2, U_MUX9.2 (A6)
M9_CH7: RV49.2, U_MUX9.4 (A7)
MUX_EN8: U_MUX8.6 (~E); also elsewhere on the board
MUX_EN9: U_MUX9.6 (~E); also elsewhere on the board
MUX_S0: U_MUX8.11 (S0), U_MUX9.11 (S0); also elsewhere on the board
MUX_S1: U_MUX8.10 (S1), U_MUX9.10 (S1); also elsewhere on the board
MUX_S2: U_MUX8.9 (S2), U_MUX9.9 (S2); also elsewhere on the board
SENSE_3: U_MUX8.3 (A), U_MUX9.3 (A); also elsewhere on the board
SM_3V3: C12.1, C13.1, RV35.3, RV36.3, RV37.3, RV38.3, RV39.3, RV40.3, RV41.3, RV42.3, RV43.3, RV44.3, RV45.3, RV46.3, RV47.3, RV48.3, RV49.3, U_MUX8.16 (VCC), U_MUX9.16 (VCC); also elsewhere on the board
